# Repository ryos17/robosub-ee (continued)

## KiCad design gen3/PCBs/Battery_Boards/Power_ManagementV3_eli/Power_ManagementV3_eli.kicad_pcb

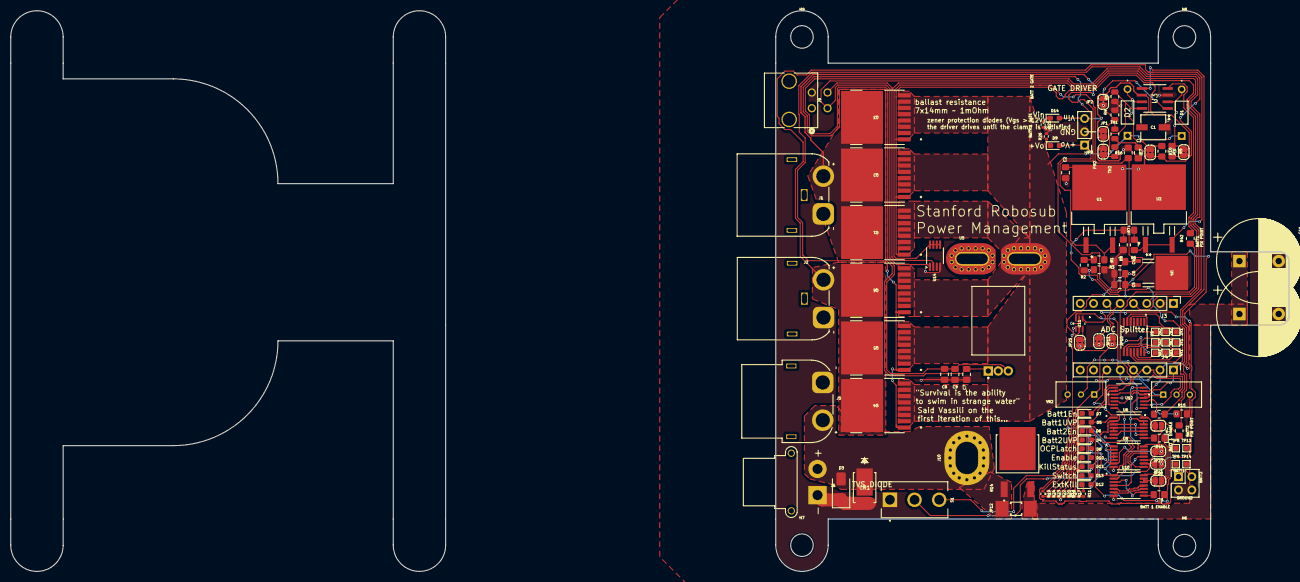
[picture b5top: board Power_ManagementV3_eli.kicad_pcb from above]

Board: 2 copper layers, 98.0 x 107.0 mm, 118 parts (0 on the bottom side), 73 nets.

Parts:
2A2, 2B2, 2Y1, 3A2, 3B2, 3Y1, 4A1, 4B1, 4Y1: TestPoint; TestPoint_Pad_1.0x1.0mm
C1: 10uF; CAP_EEE-1CA100SR_PAN
C2, C3, C4, C5: 10uF; C_0805_2012Metric_Pad1.18x1.45mm_HandSolder
C6: 1uF; C_0805_2012Metric_Pad1.18x1.45mm_HandSolder
C7: 0.1u; C_0805_2012Metric_Pad1.18x1.45mm_HandSolder
C8: 100nF; C_0805_2012Metric_Pad1.18x1.45mm_HandSolder
C9: 1µF; C_0805_2012Metric_Pad1.18x1.45mm_HandSolder
C10, C11: 10,000uF; CP_Radial_D16.0mm_P7.50mm
CR1: SBRT15U50SP5-13; POWERDI5_DIO
D1, D2: D_Zener; 1N5242B
D3: TVS; D_SMA
D4, D5, D6, D7, D8, D9, D10, D11, D12, D13, D14: GreenLED; LED_0603_1608Metric_Pad1.05x0.95mm_HandSolder
H6, H7, H8, H9: MountingHole; MountingHole_4.3mm_M4
J1, J2: Conn_01x02_Pin; AMASS_XT60IPW-M_1x03_P7.20mm_Horizontal
J3, J4: Conn_01x08; PinHeader_1x08_P2.54mm_Vertical
J5: Conn_01x02_Pin; AMASS_XT60PW-F_1x02_P7.20mm_Horizontal
J6: Conn_01x02_Pin; AMASS_XT30PW-F_1x02_P2.50mm_Horizontal
J9: Conn_01x04_Pin; CONN_SD-43045-008_04_MOL
J10: via; MountingHole_4.3x6.2mm_M4_Pad_Via
J17: FPGA MOUNT; PinHeader_2x02_P2.54mm_Vertical
JP1, JP3: SolderJumper_2_Bridged; SolderJumper-2_P1.3mm_Bridged2Bar_RoundedPad1.0x1.5mm
JP2: SolderJumper_2_Open; SolderJumper-2_P1.3mm_Open_RoundedPad1.0x1.5mm
JP6, JP7: SolderJumper-2_P1.3mm_Bridged2Bar_RoundedPad1.0x1.5mm
JP10, JP11, JP25, JP27: Jumper_2_Bridged; SolderJumper-2_P1.3mm_Bridged2Bar_RoundedPad1.0x1.5mm
JP12: Jumper_2_Open; KEYSTONE_5102
JP21, JP23, JP26: Jumper_2_Open; SolderJumper-2_P1.3mm_Open_RoundedPad1.0x1.5mm
PM2: LMS78
Q1, Q2, Q3, Q4, Q5, Q6: MCTL160N15Y-TP; TOLL-8L_MCC
R1, R6: 50k; R_0805_2012Metric_Pad1.20x1.40mm_HandSolder
R2, R3, R7, R8, R16: 10k; R_0805_2012Metric_Pad1.20x1.40mm_HandSolder
R4, R5: 100k; R_0805_2012Metric
R9, R10, R42, R43, R44, R45: 0R; R_0805_2012Metric_Pad1.20x1.40mm_HandSolder
R11, R12, R17, R18, R19, R20, R22, R23, R24: 100; R_0402_1005Metric
R13: 2.2k; R_0805_2012Metric_Pad1.20x1.40mm_HandSolder
R14: 0.5 Ohm 25W; TO508P1229X317-3N
R15: 3.9k; R_0805_2012Metric_Pad1.20x1.40mm_HandSolder
R25: 15k; R_0402_1005Metric
R26: 1.5k; R_0402_1005Metric
S1: 100SP1T1B4M2QE; SW_100SP1T1B4M2QE
TH1, TH2: Thermistor_US; R_0805_2012Metric
TP8, TP9, TP13, TP14: TestPoint; TestPoint_Pad_1.0x1.0mm
U1, U2: STPS5045SG-TR; D2PAK_STM
U3: LTC1255CS8-PBF; LTC1255
U4: BA033CC0FP-E2; TO252-3_ROM
U5: ACS758LCB-100U-PFF-T; Allegro_MicroSystems,_LLC-CB-5-PFF-0-0-MFG
U6, U8, U9, U10: SN74HC132PWR; SOP65P640X120-14N
U11: SN74LVC1G373DCKR; SN74LVC
U12: MCP6564-E/ST; TSSOP14_MC_MCH
U14: MCP9808_MSOP; MSOP-8_3x3mm_P0.65mm
VR1, VR2: 3296W-1-103RLF; TRIM_3296W-1-103RLF

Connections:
+3.3V: C5.1, C6.1, JP10.2 (B), JP21.2 (B), JP23.2 (B), R16.1, S1.3, U4.3 (OUT), U6.14 (VCC), U8.14 (VCC), U9.14 (VCC), U10.14 (VCC), U11.5 (VCC), U12.4 (VDD), U14.5 (A2), U14.6 (A1), U14.7 (A0), U14.8 (V_{DD}), VR1.1, VR2.1
+5V: C4.1, C7.2, D9.2 (A), PM2.3, U4.1 (Vcc), U5.1 (VCC)
+BATT: CR1.3, D3.2 (A), J5.2, J6.2, J10.1, JP12.2 (B), R14.1, U5.5 (IP-)
+BATT1: J1.2, Q1.9 (D), Q2.9 (D), Q3.9 (D), R1.2, U1.1 (Input), U1.3 (Input)
+BATT2: J2.2, Q4.9 (D), Q5.9 (D), Q6.9 (D), R6.1, U2.1 (Input), U2.3 (Input)
+BATTHall: D1.2 (A), D2.2 (A), Q1.2 (S), Q1.3 (S), Q1.4 (S), Q1.5 (S), Q1.6 (S), Q1.7 (S), Q1.8 (S), Q2.2 (S), Q2.3 (S), Q2.4 (S), Q2.5 (S), Q2.6 (S), Q2.7 (S), Q2.8 (S), Q3.2 (S), Q3.3 (S), Q3.4 (S), Q3.5 (S), Q3.6 (S), Q3.7 (S), Q3.8 (S), Q4.2 (S), Q4.3 (S), Q4.4 (S), Q4.5 (S), Q4.6 (S), Q4.7 (S), Q4.8 (S), Q5.2 (S), Q5.3 (S), Q5.4 (S), Q5.5 (S), Q5.6 (S), Q5.7 (S), Q5.8 (S), Q6.2 (S), Q6.3 (S), Q6.4 (S), Q6.5 (S), Q6.6 (S), Q6.7 (S), Q6.8 (S), U5.4 (IP+)
+VregDiode: C1.1, C2.1, C3.1, D14.2 (A), JP1.2 (B), JP3.2 (B), PM2.1, TH1.1, TH2.1, U1.2 (Output), U2.2 (Output), U3.6 (VS)
-BATT1: C1.2, C2.2, C3.2, C4.2, C5.2, C6.2, C7.1, C8.2, C9.2, C10.2, C11.2, CR1.1, CR1.2, D3.1 (K), J1.1, J2.1, J3.2, J5.1, J6.1, J9.2, J17.3, J17.4, JP11.2 (B), JP25.1 (A), PM2.2, R3.1, R4.1, R5.1, R8.1, R11.2, R12.1, R15.2, R16.2, R17.2, R18.2, R19.2, R20.2, R22.2, R23.2, R24.2, R25.2, R26.2, S1.1, U3.3 (GND), U4.2 (GND), U5.2 (GND), U6.7 (GND), U8.7 (GND), U9.7 (GND), U10.7 (GND), U11.2 (GND), U12.11 (VSS), U14.4 (GND), VR1.3, VR2.3
/Battery Control Logic/Batt1>UVP: D5.2 (A), U6.1 (1A), U12.8 (OUTC)
/Battery Control Logic/Batt1Disable: U10.5 (2B), U10.11 (4Y)
/Battery Control Logic/Batt2>UVP: D4.2 (A), U10.1 (1A), U12.14 (OUTD)
/Battery Control Logic/OCPReference: J4.4, U12.2 (-INA), VR2.2
/Battery Control Logic/OnboardKillSwitch: D13.2 (A), S1.2, U8.1 (1A)
/Battery Control Logic/UVPReference: J4.3, U12.9 (-INC), U12.13 (-IND), VR1.2
/Battery Control Logic/VBatt1 > VBatt2: U6.4 (2A), U6.5 (2B), U6.11 (4Y)
/Battery Control Logic/VBatt1<VBatt2: U6.12 (4A), U6.13 (4B), U10.4 (2A), U12.7 (OUTB)
/Battery Control Logic/pre_enable1: R44.2, U6.8 (3Y)
/Battery Control Logic/pre_enable2: R45.2, U10.8 (3Y)
/Battery Control Logic/~GateDisable: D10.2 (A), J4.6, U6.2 (1B), U8.11 (4Y), U10.2 (1B)
/Battery Control Logic/~OCP: J4.5, U11.3 (D), U12.1 (OUTA)
/Battery Control Logic/~SystemKill post: JP27.2 (B), U8.10 (3B)
/ENABLE_BATT1: R42.2, U3.4 (IN1)
/ENABLE_BATT2: R43.2, U3.5 (IN2)
Batt1Enable: D7.2 (A), J17.1, JP21.1 (A), R42.1, R44.1, U10.12 (4A), U10.13 (4B)
Batt1Gate: JP6.1 (A), Q1.1 (G), Q2.1 (G), Q3.1 (G), R9.2
Batt1GatePreDiv: D1.1 (K), JP6.2 (B), R9.1, U3.2 (GATE1)
Batt2Enable: D6.2 (A), J17.2, JP23.1 (A), R43.1, R45.1
Batt2Gate: JP7.1 (A), Q4.1 (G), Q5.1 (G), Q6.1 (G), R10.2
Batt2GatePreDiv: D2.1 (K), JP7.2 (B), R10.1, U3.7 (GATE2)
COM: J3.6, JP11.1 (A)
Capacitors: C10.1, C11.1, JP12.1 (A), R14.2
I2C1_SCL: J3.3, J9.4, U14.2 (SCL)
I2C1_SDA: J3.4, J9.3, U14.1 (SDA)
ISample3.3V: R13.2, R15.1, U12.3 (+INA)
ISample5V: C8.1, C9.1, R13.1, U5.3 (VIOUT)
KillSwitch: D12.2 (A), U8.2 (1B)
LETeensy: JP26.1 (A), U11.1 (LE)
unnamed: D7.1 (K), R19.1
unnamed: D9.1 (K), R26.1
unnamed: D14.1 (K), R25.1
unnamed: JP1.1 (A), JP2.1 (A), R4.2, TH1.2, U3.1 (DS1)
unnamed: JP2.2 (B), JP3.1 (A), R5.2, TH2.2, U3.8 (DS2)
unnamed: JP25.2 (B), U11.6 (*OE)
unnamed: R1.1, R2.1
unnamed: R6.2, R7.2
unnamed: U6.3 (1Y), U6.9 (3A)
unnamed: U6.6 (2Y), U6.10 (3B)
unnamed: U8.3 (1Y), U8.4 (2A), U8.5 (2B)
unnamed: U8.8 (3Y), U8.12 (4A), U8.13 (4B)
unnamed: 2A2.1, U9.4 (2A)
unnamed: 2B2.1, U9.5 (2B)
unnamed: 2Y1.1, U9.6 (2Y)
unnamed: 3A2.1, U9.9 (3A)
unnamed: 3B2.1, U9.10 (3B)
unnamed: 3Y1.1, U9.8 (3Y)
unnamed: 4A1.1, U9.12 (4A)
unnamed: 4B1.1, U9.13 (4B)
unnamed: 4Y1.1, U9.11 (4Y)
unnamed: U10.3 (1Y), U10.9 (3A)
unnamed: U10.6 (2Y), U10.10 (3B)
RArray1: D12.1 (K), R11.1
RArray2: D13.1 (K), R12.2
RArray3: D11.1 (K), R17.1
RArray4: D10.1 (K), R18.1
RArray5: D8.1 (K), R20.1
RArray6: D4.1 (K), R22.1
RArray7: D6.1 (K), R23.1
RArray8: D5.1 (K), R24.1
REF: J3.5, JP10.1 (A)
VSampleBatt1: J4.2, R2.2, R3.2, U12.6 (-INB), U12.10 (+INC)
VSampleBatt2: J4.1, R7.1, R8.2, U12.5 (+INB), U12.12 (+IND)
~OCPLatch: D8.2 (A), JP26.2 (B), U8.9 (3A), U11.4 (Q)
~SystemKill: D11.2 (A), JP27.1 (A), U8.6 (2Y)

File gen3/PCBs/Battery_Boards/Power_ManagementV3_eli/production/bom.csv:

Designator,Footprint,Quantity,Value,LCSC Part #
"2A2, 2B2, 2Y1, 3A2, 3B2, 3Y1, 4A1, 4B1, 4Y1, TP13, TP14, TP8, TP9",TestPoint_Pad_1.0x1.0mm,13,TestPoint,
C1,CAP_EEE-1CA100SR_PAN,1,10uF,
"C10, C11",CP_Radial_D16.0mm_P7.50mm,2,"10,000uF",
"C2, C3, C4, C5",0805,4,10uF,
C6,0805,1,1uF,
C7,0805,1,0.1u,
C8,0805,1,100nF,
C9,0805,1,1µF,
CR1,POWERDI5_DIO,1,SBRT15U50SP5-13,
"D1, D2",1N5242B,2,D_Zener,
"D10, D11, D12, D13, D14, D4, D5, D6, D7, D8, D9",0603,11,GreenLED,
D3,D_SMA,1,TVS,
"H6, H7, H8, H9",MountingHole_4.3mm_M4,4,MountingHole,
"J1, J2",AMASS_XT60IPW-M_1x03_P7.20mm_Horizontal,2,Conn_01x02_Pin,
J10,MountingHole_4.3x6.2mm_M4_Pad_Via,1,via,
J17,PinHeader_2x02_P2.54mm_Vertical,1,FPGA MOUNT,
"J3, J4",PinHeader_1x08_P2.54mm_Vertical,2,Conn_01x08,
J5,AMASS_XT60PW-F_1x02_P7.20mm_Horizontal,1,Conn_01x02_Pin,
J6,AMASS_XT30PW-F_1x02_P2.50mm_Horizontal,1,Conn_01x02_Pin,
J9,CONN_SD-43045-008_04_MOL,1,Conn_01x04_Pin,
"JP10, JP11, JP25, JP27",SolderJumper-2_P1.3mm_Bridged2Bar_RoundedPad1.0x1.5mm,4,Jumper_2_Bridged,
JP12,KEYSTONE_5102,1,Jumper_2_Open,
"JP21, JP23, JP26",SolderJumper-2_P1.3mm_Open_RoundedPad1.0x1.5mm,3,Jumper_2_Open,
"JP6, JP7",SolderJumper-2_P1.3mm_Bridged2Bar_RoundedPad1.0x1.5mm,2,~,
PM2,LMS78,1,LMS78,
"Q1, Q2, Q3, Q4, Q5, Q6",TOLL-8L_MCC,6,MCTL160N15Y-TP,
"R1, R6",0805,2,50k,
"R10, R42, R43, R44, R45, R9",0805,6,0R,
"R11, R12, R17, R18, R19, R20, R22, R23, R24",0402,9,100,
R13,0805,1,2.2k,
R14,TO508P1229X317-3N,1,0.5 Ohm 25W,
R15,0805,1,3.9k,
"R16, R2, R3, R7, R8",0805,5,10k,
R25,0402,1,15k,
R26,0402,1,1.5k,
"R4, R5",0805,2,100k,
S1,SW_100SP1T1B4M2QE,1,100SP1T1B4M2QE,
"TH1, TH2",0805,2,Thermistor_US,
"U1, U2",D2PAK_STM,2,STPS5045SG-TR,
"U10, U6, U8, U9",SOP65P640X120-14N,4,SN74HC132PWR,
U11,SN74LVC,1,SN74LVC1G373DCKR,
U12,TSSOP14_MC_MCH,1,MCP6564-E/ST,
U14,MSOP-8_3x3mm_P0.65mm,1,MCP9808_MSOP,
U3,LTC1255,1,LTC1255CS8-PBF,
U4,TO252-3_ROM,1,BA033CC0FP-E2,
U5,"Allegro_MicroSystems,_LLC-CB-5-PFF-0-0-MFG",1,ACS758LCB-100U-PFF-T,
"VR1, VR2",TRIM_3296W-1-103RLF,2,3296W-1-103RLF,

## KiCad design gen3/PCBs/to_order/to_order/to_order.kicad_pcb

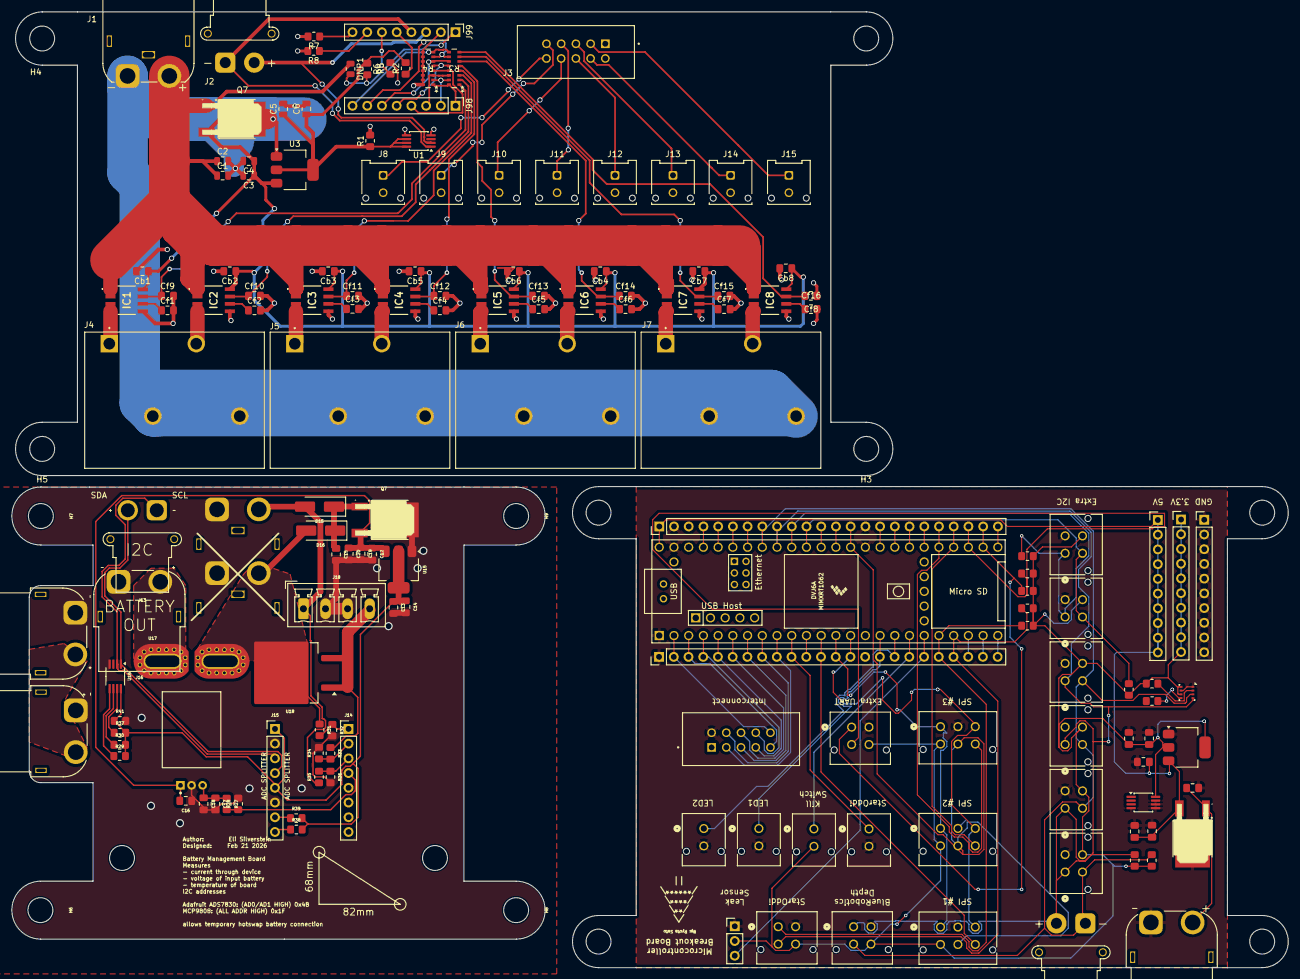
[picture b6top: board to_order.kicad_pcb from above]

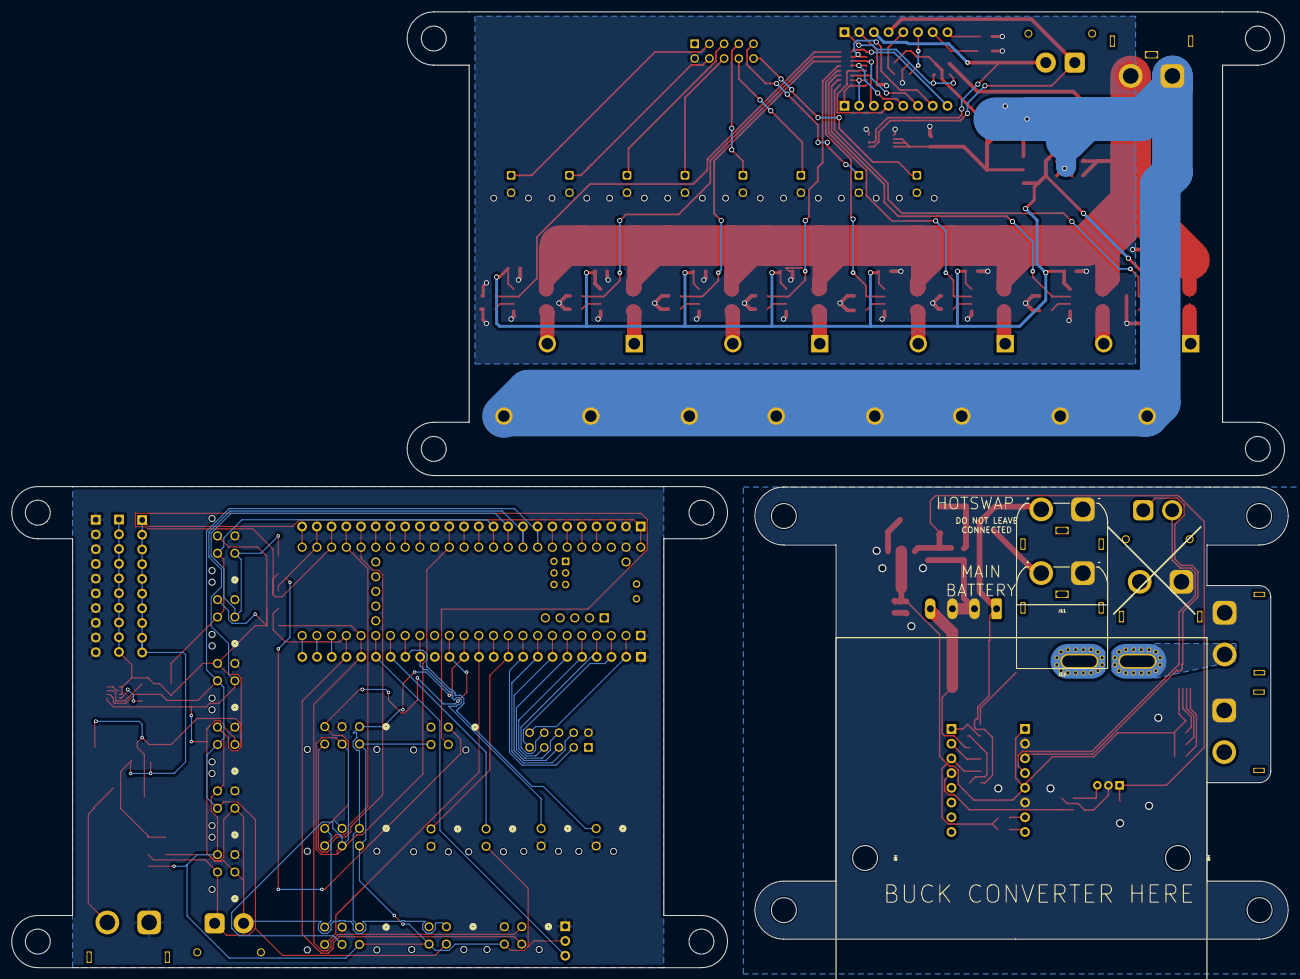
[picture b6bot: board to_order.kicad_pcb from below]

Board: 2 copper layers, 220.2 x 164.9 mm, 166 parts (4 on the bottom side), 109 nets.

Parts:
C1, C12, C12#2, C13, C13#2, C15, C15#2, C19: 10uF; C_0805_2012Metric_Pad1.18x1.45mm_HandSolder
C1#2, C3, C5: 1 µF; C_0805_2012Metric
C2, C14, C14#2, C20: 1uF; C_0805_2012Metric_Pad1.18x1.45mm_HandSolder
C2#2, C4, C6: 10 µF; C_0805_2012Metric
C16: 0.1uF; C_0805_2012Metric_Pad1.18x1.45mm_HandSolder
C17: 100nF; C_0805_2012Metric_Pad1.18x1.45mm_HandSolder
C18: 1µF; C_0805_2012Metric_Pad1.18x1.45mm_HandSolder
Cb1, Cb2, Cb3, Cb4, Cb5, Cb6, Cb7, Cb8: 0.1 µF; C_0805_2012Metric_Pad1.18x1.45mm_HandSolder
Cf1, Cf2, Cf3, Cf4, Cf5, Cf6, Cf7, Cf8: 100 nF; C_0805_2012Metric_Pad1.18x1.45mm_HandSolder
Cf9, Cf10, Cf11, Cf12, Cf13, Cf14, Cf15, Cf16: 1 µF; C_0805_2012Metric_Pad1.18x1.45mm_HandSolder
D15, D16: SS54; D_SMA_Handsoldering
DNP1: 0; R_0805_2012Metric
H2, H3, H4, H5, H6, H6#2, H7, H7#2, H8, H8#2, H8#3, H8#4, H9, H9#2: MountingHole; MountingHole_4.3mm_M4
IC1, IC2, IC3, IC4, IC5, IC6, IC7, IC8: ACS713ELCTR-30A-T; ACS711ELCTR25ABT
J1, J11#3, J12#3: Conn_01x02_Pin; AMASS_XT60IPW-M_1x03_P7.20mm_Horizontal
J1#2: BlueRobotics Depth Sensor; CONN_SD-43045-005_04_MOL
J2, J13#2: Conn_01x02_Pin; AMASS_XT30PW-F_1x02_P2.50mm_Horizontal
J2#2: Interconnect; SULLINS_SBH11-PBPC-D05-ST-BK
J3: External Battery; AMASS_XT60PW-F_1x02_P7.20mm_Horizontal
J3#2: SBH11-PBPC-D05-ST-BK; SULLINS_SBH11-PBPC-D05-ST-BK
J4, J5#2, J6, J7#2: 1098169; PHOENIX_1098169
J4#2, J6#2: Conn_01x24; PinHeader_1x24_P2.54mm_Vertical
J5: External I2C; AMASS_XT30PW-F_1x02_P2.50mm_Horizontal
J7: Extra I2C #1; CONN_SD-43045-005_04_MOL
J8: 0430450212; Molex_Micro-Fit_3.0_43045-0212_2x01_P3.00mm_Vertical
J8#2: Extra I2C #2; CONN_SD-43045-005_04_MOL
J9: Lumen PWM; CONN_SD-43045-005_02_MOL
J9#2, J10, J11#2, J12#2, J13#3, J14#2, J15: 430450228; Molex_Micro-Fit_3.0_43045-0212_2x01_P3.00mm_Vertical
J10#2: Kill Switch; CONN_SD-43045-005_02_MOL
J11: StarOddi CTD Comms; CONN_SD-43045-005_04_MOL
J12: LED1; CONN_SD-43045-005_02_MOL
J13: LED2; CONN_SD-43045-005_02_MOL
J14: Leak Sensor; PinHeader_1x03_P2.54mm_Vertical
J14#3, J15#2, J98, J99: Conn_01x08; PinHeader_1x08_P2.54mm_Vertical
J15#3: Extra I2C #3; CONN_SD-43045-005_04_MOL
J16: Extra I2C #6; CONN_SD-43045-005_04_MOL
J16#2, J21#2, J22: Conn_01x02_Pin; AMASS_XT60PW-F_1x02_P7.20mm_Horizontal
J17: Extra I2C #5; CONN_SD-43045-005_04_MOL
J18: Extra I2C #4; CONN_SD-43045-005_04_MOL
J18#2: Conn_01x04_Socket; PhoenixContact_MCV_1,5_4-G-3.81_1x04_P3.81mm_Vertical
J19: GND Line; PinHeader_1x10_P2.54mm_Vertical
J20: 3.3V Line; PinHeader_1x10_P2.54mm_Vertical
J21: 5V Line; PinHeader_1x10_P2.54mm_Vertical
J22#2: Extra SPI #1; CONN_SD-43045-005_06_MOL
J23: Extra SPI #2; CONN_SD-43045-005_06_MOL
J24: Extra SPI #3; CONN_SD-43045-005_06_MOL
J25: Secondary UART; CONN_SD-43045-005_04_MOL
Q7, Q7#2, Q7#3: L78M05ABDT-TR; TO-252-2_L6.5-W6.1-P4.58-LS10.0-TL
R1, R2, R3#2, R4#2, R5#2, R6#2, R7, R8, R10, R11, R27, R32, R34, R36, R41: 10k; R_0805_2012Metric_Pad1.20x1.40mm_HandSolder
R1#2, R2#2, R5, R6, R7#2, R8#2, R29, R30, R37, R38, R39: 0R; R_0805_2012Metric_Pad1.20x1.40mm_HandSolder
R3: 2.2k Array; 2506_8x_Resistor_Array
R4: 3.3k Array; 2506_8x_Resistor_Array
R28: 20k; R_0805_2012Metric_Pad1.20x1.40mm_HandSolder
R31, R33, R35: 47k; R_0805_2012Metric_Pad1.20x1.40mm_HandSolder
U1, U2, U16: MCP9808_MSOP; MSOP-8_3x3mm_P0.65mm
U3, U15, U15#2: AMS1117-3.3; SOT-223-3_TabPin2
U4: BME280; Bosch_LGA-8_2.5x2.5mm_P0.65mm_ClockwisePinNumbering
U6: Teensy4.1; Teensy41
U17: ACS758LCB-100U-PFF-T; Allegro_MicroSystems,_LLC-CB-5-PFF-0-0-MFG
U18: SRT60L100DC-R; TO-263-2

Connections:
+3.3V: C5.1, C6.1, C13#2.1, C14#2.1, J1#2.4, J7.4, J8#2.4, J10#2.2, J11.4, J14.2, J15#3.4, J16.4, J17.4, J18.4, J20.1, J20.2, J20.3, J20.4, J20.5, J20.6, J20.7, J20.8, J20.9, J20.10, J22#2.4, J23.4, J24.4, J25.4, R1.1, R2.1, R2#2.2, R3#2.1, R4#2.1, R5#2.1, R6.1, R6#2.1, R7.2, R8.2, R10.2, R11.2, U1.6 (A1), U1.7 (A0), U1.8 (V_{DD}), U2.8 (V_{DD}), U3.2 (VO), U4.6 (VDDIO), U4.8 (VDD), U15.2 (VO)
+3.3V_: C13.1, C14.1, J15#2.1, J15#2.5, R29.2, R30.2, R37.2, R38.2, R39.2, R41.1, U15#2.2 (VO), U16.8 (V_{DD})
+5V: C1.1, C2.1, C3.1, C4.1, C12.1, Cb1.1, Cb2.1, Cb3.1, Cb4.1, Cb5.1, Cb6.1, Cb7.1, Cb8.1, DNP1.1, IC1.8 (VCC), IC2.8 (VCC), IC3.8 (VCC), IC4.8 (VCC), IC5.8 (VCC), IC6.8 (VCC), IC7.8 (VCC), IC8.8 (VCC), J6#2.1, J21.1, J21.2, J21.3, J21.4, J21.5, J21.6, J21.7, J21.8, J21.9, J21.10, Q7#2.3 (OUT), Q7#3.3 (OUT), U3.3 (VI), U6.48 (VIN), U15.3 (VI)
+5V_: C12#2.1, C16.2, C19.1, C20.1, Q7.3 (OUT), U15#2.3 (VI), U17.1 (VCC)
+BATT: C1#2.1, C2#2.1, D16.2 (A), IC1.1 (IP+_1), IC1.2 (IP+_2), IC2.1 (IP+_1), IC2.2 (IP+_2), IC3.1 (IP+_1), IC3.2 (IP+_2), IC4.1 (IP+_1), IC4.2 (IP+_2), IC5.1 (IP+_1), IC5.2 (IP+_2), IC6.1 (IP+_1), IC6.2 (IP+_2), IC7.1 (IP+_1), IC7.2 (IP+_2), IC8.1 (IP+_1), IC8.2 (IP+_2), J1.2, J12#3.2, Q7#3.1 (IN), R31.1, U17.4 (IP+), U18.2 (Output)
+BATT_out: J16#2.2, J21#2.2, J22.2, U17.5 (IP-)
+EXT_LV_SUPPLY: J18#2.4, R33.1, U18.1 (Input), U18.3 (Input)
+TEMP_BATT: D15.2 (A), J11#3.2, J18#2.1, R35.1
-BATT: C1#2.2, C2#2.2, C3.2, C4.2, C5.2, C6.2, J1.1, J4.2, J4.4, J5#2.2, J5#2.4, J6.2, J6.4, J7#2.2, J7#2.4, Q7#3.4 (GND), U3.1 (GND)
/SCL: J13#2.1, J15#2.3, U16.2 (SCL)
/SDA: J13#2.2, J15#2.4, U16.1 (SDA)
AD0: J99.7, R8#2.1
AD1: J99.8, R7#2.1
COM: J99.6, R5.1
Dled1: J4#2.16, J12.1, U6.16 (24_A10_TX6_SCL2)
Dled2: J4#2.17, J13.1, U6.17 (25_A11_RX6_SDA2)
Dswitch1: J4#2.18, J10#2.1, U6.18 (26_A12_MOSI1)
GND: C1.2, C2.2, C12.2, C13#2.2, C14#2.2, C15#2.2, Cb1.2, Cb2.2, Cb3.2, Cb4.2, Cb5.2, Cb6.2, Cb7.2, Cb8.2, Cf1.2, Cf2.2, Cf3.2, Cf4.2, Cf5.2, Cf6.2, Cf7.2, Cf8.2, Cf9.2, Cf10.2, Cf11.2, Cf12.2, Cf13.2, Cf14.2, Cf15.2, Cf16.2, IC1.5 (GND), IC2.5 (GND), IC3.5 (GND), IC4.5 (GND), IC5.5 (GND), IC6.5 (GND), IC7.5 (GND), IC8.5 (GND), J1#2.2, J2#2.2, J3.1, J3#2.2, J4#2.1, J6#2.2, J6#2.15, J7.2, J8.2, J8#2.2, J9.2, J9#2.2, J10.2, J11.2, J11#2.2, J12.2, J12#2.2, J13.2, J13#3.2, J14.1, J14#2.2, J15.2, J15#3.2, J16.2, J17.2, J18.2, J19.1, J19.2, J19.3, J19.4, J19.5, J19.6, J19.7, J19.8, J19.9, J19.10, J22#2.2, J23.2, J24.2, J25.2, J99.2, Q7#2.4 (GND), R1.2, R4.9, R4.10, R4.11, R4.12, R4.13, R4.14, R4.15, R4.16, R5.2, R7#2.2, R8#2.2, U1.4 (GND), U1.5 (A2), U2.4 (GND), U2.5 (A2), U2.6 (A1), U2.7 (A0), U4.1 (GND), U4.7 (GND), U6.1 (GND), U6.34 (GND), U6.47 (GND), U15.1 (GND)
GND_bak: C12#2.2, C13.2, C14.2, C15.2, C16.1, C17.2, C18.2, C19.2, C20.2, J11#3.1, J12#3.1, J15#2.2, J15#2.6, J16#2.1, J18#2.2, J18#2.3, J21#2.1, J22.1, Q7.4 (GND), R28.2, R32.2, R34.2, R36.2, R41.2, U15#2.1 (GND), U16.4 (GND), U17.2 (GND)
I2C1_SCL: J1#2.3, J5.1, J6#2.8, J7.3, J8#2.3, J15#3.3, J18.3, R5#2.2, U4.3 (SDI), U6.41 (19_A5_SCL)
I2C1_SDA: J1#2.1, J5.2, J6#2.9, J7.1, J8#2.1, J15#3.1, J18.1, R4#2.2, U4.4 (SCK), U6.40 (18_A4_SDA)
I2C2_SCL: J6#2.11, J16.3, J17.3, R3#2.2, U6.38 (16_A2_RX4_SCL1)
I2C2_SDA: J6#2.10, J16.1, J17.1, R6#2.2, U6.39 (17_A3_TX4_SDA1)
Lumen_PWM: J4#2.10, J9.1, U6.10 (8_TX2_IN1)
unnamed: C15.1, D15.1 (K), D16.1 (K), Q7.1 (IN)
unnamed: Cf1.1, IC1.6 (FILTER)
unnamed: Cf2.1, IC2.6 (FILTER)
unnamed: Cf3.1, IC3.6 (FILTER)
unnamed: Cf4.1, IC4.6 (FILTER)
unnamed: Cf5.1, IC5.6 (FILTER)
unnamed: Cf6.1, IC6.6 (FILTER)
unnamed: Cf7.1, IC7.6 (FILTER)
unnamed: Cf8.1, IC8.6 (FILTER)
unnamed: J14#3.1, R31.2, R32.1
unnamed: J14#3.2, R33.2, R34.1
unnamed: J14#3.3, R35.2, R36.1
unnamed: J15#2.7, R39.1
unnamed: J15#2.8, R38.1
unnamed: DNP1.2, J99.1, R6.2
unnamed: R2.2, U4.2 (CSB)
unnamed: R1#2.2, U4.5 (SDO)
unnamed: R37.1, U16.7 (A0)
unnamed: R30.1, U16.6 (A1)
unnamed: R29.1, U16.5 (A2)
PIN9: J4#2.11, U6.11 (9_OUT1C)
PIN14: J6#2.13, U6.36 (14_A0_TX3_SPDIF_OUT)
PIN15: J6#2.12, U6.37 (15_A1_RX3_SPDIF_IN)
PIN20: J6#2.7, U6.42 (20_A6_TX5_LRCLK1)
PIN21: J6#2.6, U6.43 (21_A7_RX5_BCLK1)
PIN22: J6#2.5, U6.44 (22_A8_CTX1)
PIN23: J6#2.4, U6.45 (23_A9_CRX1_MCLK1)
PIN30: J4#2.22, U6.22 (30_CRX3)
PIN31: J4#2.23, U6.23 (31_CTX3)
PIN32: J4#2.24, U6.24 (32_OUT1B)
PIN33: J6#2.24, U6.25 (33_MCLK2)
PIN38: J6#2.19, U6.30 (38_CS1_IN1)
PIN39: J6#2.18, U6.31 (39_MISO1_OUT1A)
PIN40: J6#2.17, U6.32 (40_A16)
PIN41: J6#2.16, U6.33 (41_A17)
PWM0: J2#2.10, J4#2.2, U6.2 (0_RX1_CRX2_CS1)
PWM1: J2#2.9, J3#2.10, J4#2.3, J8.1, U6.3 (1_TX1_CTX2_MISO1)
PWM2: J2#2.8, J3#2.9, J4#2.4, J9#2.1, U6.4 (2_OUT2)
PWM3: J2#2.7, J3#2.8, J4#2.5, J10.1, U6.5 (3_LRCLK2)
PWM4: J2#2.6, J3#2.7, J4#2.6, J11#2.1, U6.6 (4_BCLK2)
PWM5: J2#2.5, J3#2.6, J4#2.7, J12#2.1, U6.7 (5_IN2)
PWM6: J2#2.4, J3#2.5, J4#2.8, J13#3.1, U6.8 (6_OUT1D)
PWM7: J2#2.3, J3#2.4, J4#2.9, J14#2.1, U6.9 (7_RX2_OUT1A)
PWM8: J3#2.3, J15.1
PWR1: IC1.3 (IP-_1), IC1.4 (IP-_2), J4.1
PWR2: IC2.3 (IP-_1), IC2.4 (IP-_2), J4.3
PWR3: IC3.3 (IP-_1), IC3.4 (IP-_2), J5#2.1
PWR4: IC4.3 (IP-_1), IC4.4 (IP-_2), J5#2.3
PWR5: IC5.3 (IP-_1), IC5.4 (IP-_2), J6.1
PWR6: IC6.3 (IP-_1), IC6.4 (IP-_2), J6.3
PWR7: IC7.3 (IP-_1), IC7.4 (IP-_2), J7#2.1
PWR8: IC8.3 (IP-_1), IC8.4 (IP-_2), J7#2.3
REF: J99.5, R2#2.1
SCL: J2.2, J99.3, U1.2 (SCL)
SDA: J2.1, J99.4, U1.1 (SDA)
SPI_CS1: J4#2.12, J22#2.6, U6.12 (10_CS_MQSR)
SPI_CS2: J6#2.21, J23.6, U6.28 (36_CS)
SPI_CS3: J6#2.20, J24.6, U6.29 (37_CS)
SPI_MISO: J4#2.14, J22#2.3, J23.3, J24.3, U6.14 (12_MISO_MQSL)
SPI_MOSI: J4#2.13, J22#2.1, J23.1, J24.1, U6.13 (11_MOSI_CTX1)
SPI_SCK: J6#2.14, J22#2.5, J23.5, J24.5, U6.35 (13_SCK_LED)
UART_RX1: J4#2.20, J11.1, R11.1, U6.20 (28_RX7)
UART_RX2: J6#2.23, J25.1, R8.1, U6.26 (34_RX8)
UART_TX1: J4#2.21, J11.3, R10.1, U6.21 (29_TX7)
UART_TX2: J6#2.22, J25.3, R7.1, U6.27 (35_TX8)
VIout1: Cf9.1, IC1.7 (VIOUT), R3.1
VIout1Div: J98.1, R3.16, R4.1
VIout2: Cf10.1, IC2.7 (VIOUT), R3.2
VIout2Div: J98.2, R3.15, R4.2
VIout3: Cf11.1, IC3.7 (VIOUT), R3.3
VIout3Div: J98.3, R3.14, R4.3
VIout4: Cf12.1, IC4.7 (VIOUT), R3.4
VIout4Div: J98.4, R3.13, R4.4
VIout5: Cf13.1, IC5.7 (VIOUT), R3.5
VIout5Div: J98.5, R3.12, R4.5
VIout6: Cf14.1, IC6.7 (VIOUT), R3.6
VIout6Div: J98.6, R3.11, R4.6
VIout7: Cf15.1, IC7.7 (VIOUT), R3.7
VIout7Div: J98.7, R3.10, R4.7
VIout8: Cf16.1, IC8.7 (VIOUT), R3.8
VIout8Div: J98.8, R3.9, R4.8
V_BATT: C15#2.1, J3.2, Q7#2.1 (IN)
current_sensor_3v3: J14#3.4, R27.2, R28.1
current_sensor_5v: C17.1, C18.1, R27.1, U17.3 (VIOUT)
xDleak: J4#2.19, J14.3, U6.19 (27_A13_SCK1)

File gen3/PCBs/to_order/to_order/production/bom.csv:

Designator,Footprint,Quantity,Value,LCSC Part #
"C1_2, C12_2, C12, C13_2, C13, C15_2, C15, C19",0805,8,10uF,
"C1, C3, C5, CF10, CF11, CF12, CF13, CF14, CF15, CF16, CF9",0805,11,1 µF,
"C14_2, C14, C2_2, C20",0805,4,1uF,
C16,0805,1,0.1uF,
C17,0805,1,100nF,
C18,0805,1,1µF,
"C2, C4, C6",0805,3,10 µF,
"CB1, CB2, CB3, CB4, CB5, CB6, CB7, CB8",0805,8,0.1 µF,
"CF1, CF2, CF3, CF4, CF5, CF6, CF7, CF8",0805,8,100 nF,
"D15, D16",D_SMA_Handsoldering,2,SS54,
DNP1,0805,1,0,
"H2, H3, H4, H5, H6_2, H6, H7_2, H7, H8_4, H8_3, H8_2, H8, H9_2, H9",MountingHole_4.3mm_M4,14,MountingHole,
"IC1, IC2, IC3, IC4, IC5, IC6, IC7, IC8",ACS711ELCTR25ABT,8,ACS713ELCTR-30A-T,
"J1_2, J11, J12",AMASS_XT60IPW-M_1x03_P7.20mm_Horizontal,3,Conn_01x02_Pin,
J1,CONN_SD-43045-005_04_MOL,1,BlueRobotics Depth Sensor,
"J10_2, J11_2, J12_2, J13, J14_2, J15_3, J9",Molex_Micro-Fit_3.0_43045-0212_2x01_P3.00mm_Vertical,7,430450228,
J10,CONN_SD-43045-005_02_MOL,1,Kill Switch,
J11_3,CONN_SD-43045-005_04_MOL,1,StarOddi CTD Comms,
J12_3,CONN_SD-43045-005_02_MOL,1,LED1,
J13_3,CONN_SD-43045-005_02_MOL,1,LED2,
"J13_2, J2_2",AMASS_XT30PW-F_1x02_P2.50mm_Horizontal,2,Conn_01x02_Pin,
J14_3,PinHeader_1x03_P2.54mm_Vertical,1,Leak Sensor,
"J14, J15_2, J98, J99",PinHeader_1x08_P2.54mm_Vertical,4,Conn_01x08,
J15,CONN_SD-43045-005_04_MOL,1,Extra I2C #3,
J16_2,CONN_SD-43045-005_04_MOL,1,Extra I2C #6,
"J16, J21, J22_2",AMASS_XT60PW-F_1x02_P7.20mm_Horizontal,3,Conn_01x02_Pin,
J17,CONN_SD-43045-005_04_MOL,1,Extra I2C #5,
J18_2,CONN_SD-43045-005_04_MOL,1,Extra I2C #4,
J18,"PhoenixContact_MCV_1,5_4-G-3.81_1x04_P3.81mm_Vertical",1,Conn_01x04_Socket,
J19,PinHeader_1x10_P2.54mm_Vertical,1,GND Line,
J2,SULLINS_SBH11-PBPC-D05-ST-BK,1,Interconnect,
J20,PinHeader_1x10_P2.54mm_Vertical,1,3.3V Line,
J21_2,PinHeader_1x10_P2.54mm_Vertical,1,5V Line,
J22,CONN_SD-43045-005_06_MOL,1,Extra SPI #1,
J23,CONN_SD-43045-005_06_MOL,1,Extra SPI #2,
J24,CONN_SD-43045-005_06_MOL,1,Extra SPI #3,
J25,CONN_SD-43045-005_04_MOL,1,Secondary UART,
J3_2,AMASS_XT60PW-F_1x02_P7.20mm_Horizontal,1,External Battery,
J3,SULLINS_SBH11-PBPC-D05-ST-BK,1,SBH11-PBPC-D05-ST-BK,
"J4_2, J5, J6_2, J7",PHOENIX_1098169,4,1098169,
"J4, J6",PinHeader_1x24_P2.54mm_Vertical,2,Conn_01x24,
J5_2,AMASS_XT30PW-F_1x02_P2.50mm_Horizontal,1,External I2C,
J7_2,CONN_SD-43045-005_04_MOL,1,Extra I2C #1,
J8_2,Molex_Micro-Fit_3.0_43045-0212_2x01_P3.00mm_Vertical,1,0430450212,
J8,CONN_SD-43045-005_04_MOL,1,Extra I2C #2,
J9_2,CONN_SD-43045-005_02_MOL,1,Lumen PWM,
"Q7_3, Q7_2, Q7",TO-252-2_L6.5-W6.1-P4.58-LS10.0-TL,3,L78M05ABDT-TR,C58069
"R1_2, R10, R11, R2_2, R27, R3, R32, R34, R36, R4, R41, R5, R6, R7_2, R8_2",0805,15,10k,
"R1, R2, R29, R30, R37, R38, R39, R5_2, R6_2, R7, R8",0805,11,0R,
R28,0805,1,20k,
R3_2,2506_8x_Resistor_Array,1,2.2k Array,
"R31, R33, R35",0805,3,47k,
R4_2,2506_8x_Resistor_Array,1,3.3k Array,
"U1, U16, U2",MSOP-8_3x3mm_P0.65mm,3,MCP9808_MSOP,
"U15_2, U15, U3",SOT-223-3_TabPin2,3,AMS1117-3.3,
U17,"Allegro_MicroSystems,_LLC-CB-5-PFF-0-0-MFG",1,ACS758LCB-100U-PFF-T,
U18,TO-263-2,1,SRT60L100DC-R,
U4,Bosch_LGA-8_2.5x2.5mm_P0.65mm_ClockwisePinNumbering,1,BME280,
U6,Teensy41,1,Teensy4.1,

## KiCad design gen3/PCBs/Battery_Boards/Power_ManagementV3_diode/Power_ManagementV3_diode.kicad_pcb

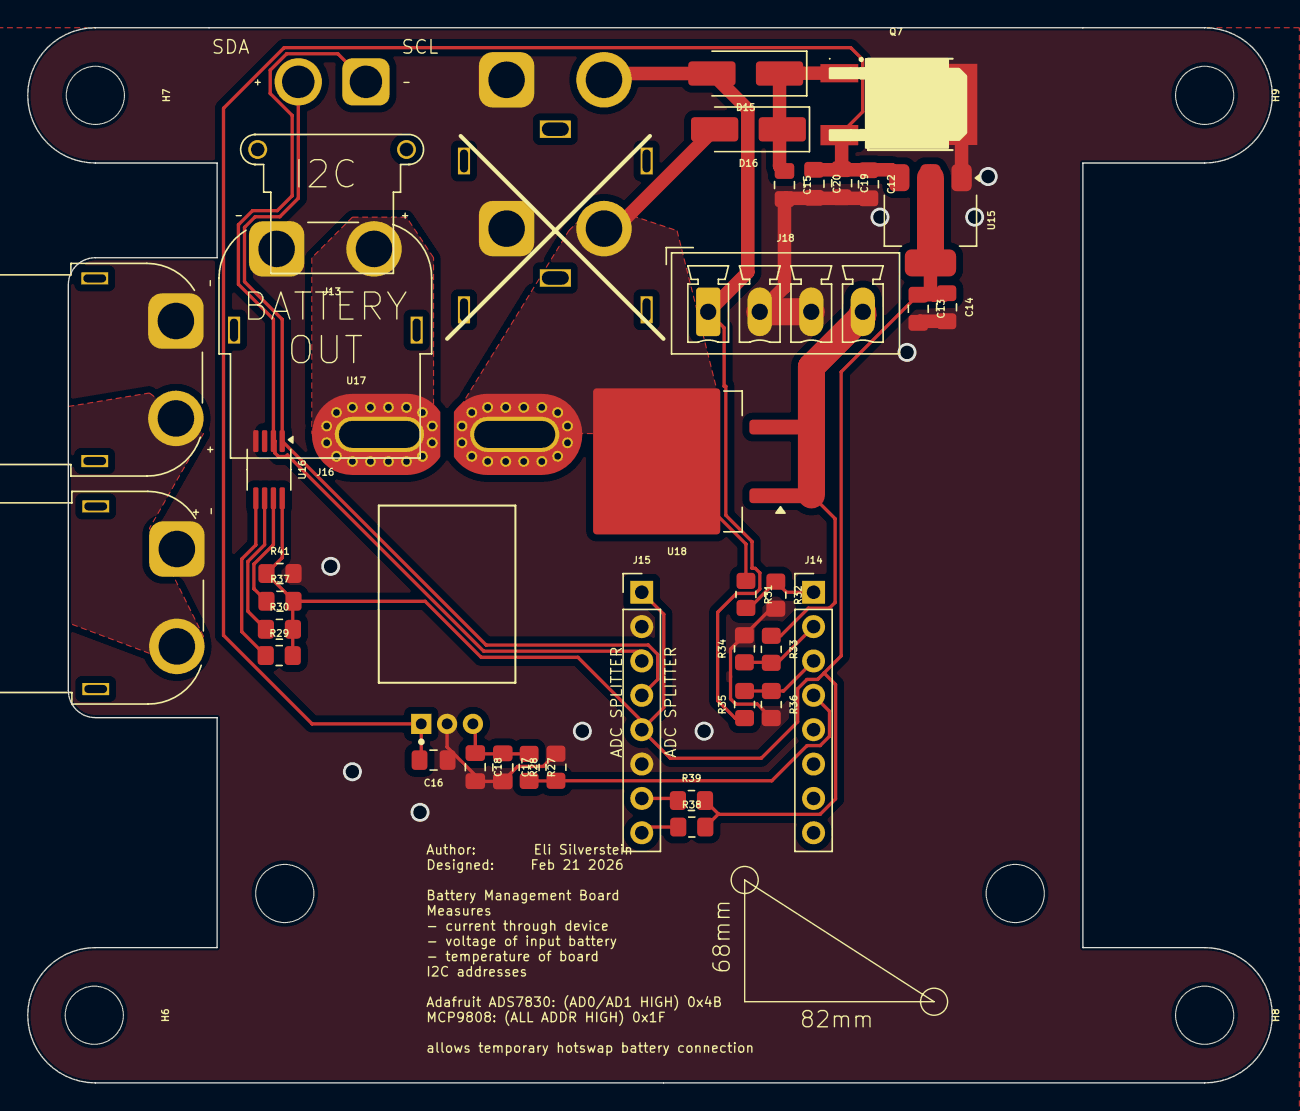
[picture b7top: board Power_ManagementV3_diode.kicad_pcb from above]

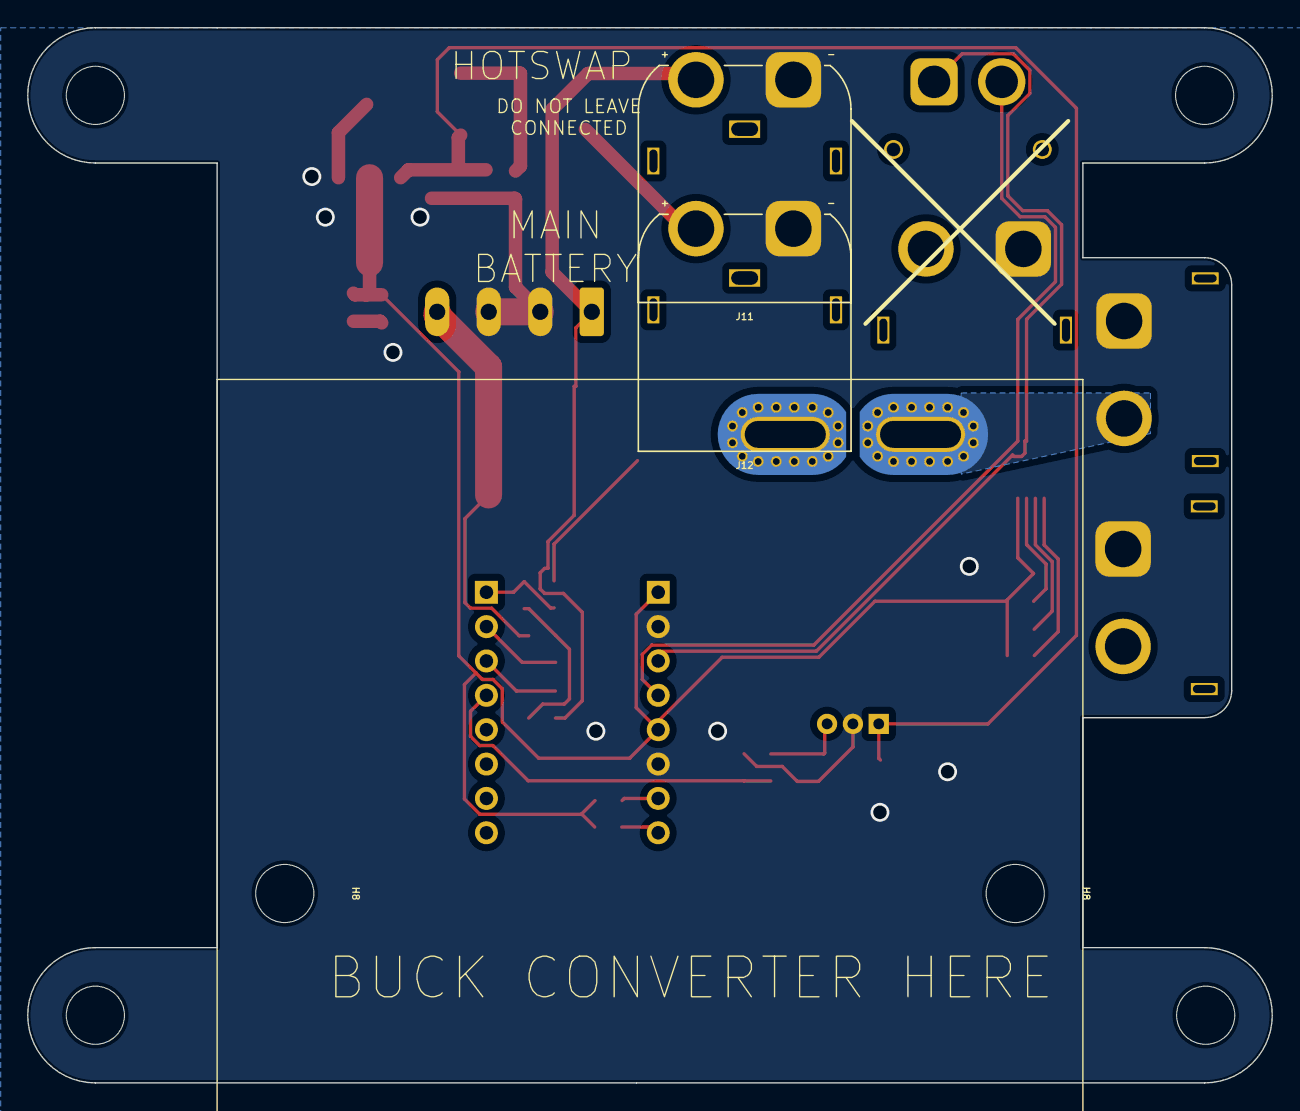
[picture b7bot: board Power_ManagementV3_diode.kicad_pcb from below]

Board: 2 copper layers, 92.0 x 78.0 mm, 45 parts (4 on the bottom side), 20 nets.

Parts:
C12, C13, C15, C19: 10uF; C_0805_2012Metric_Pad1.18x1.45mm_HandSolder
C14, C20: 1uF; C_0805_2012Metric_Pad1.18x1.45mm_HandSolder
C16: 0.1uF; C_0805_2012Metric_Pad1.18x1.45mm_HandSolder
C17: 100nF; C_0805_2012Metric_Pad1.18x1.45mm_HandSolder
C18: 1µF; C_0805_2012Metric_Pad1.18x1.45mm_HandSolder
D15, D16: SS54; D_SMA_Handsoldering
H6, H7, H8, H8#2, H8#3, H9: MountingHole; MountingHole_4.3mm_M4
J11, J12: Conn_01x02_Pin; AMASS_XT60IPW-M_1x03_P7.20mm_Horizontal
J13: Conn_01x02_Pin; AMASS_XT30PW-F_1x02_P2.50mm_Horizontal
J14, J15: Conn_01x08; PinHeader_1x08_P2.54mm_Vertical
J16, J21, J22: Conn_01x02_Pin; AMASS_XT60PW-F_1x02_P7.20mm_Horizontal
J18: Conn_01x04_Socket; PhoenixContact_MCV_1,5_4-G-3.81_1x04_P3.81mm_Vertical
Q7: L78M05ABDT-TR; TO-252-2_L6.5-W6.1-P4.58-LS10.0-TL
R27, R32, R34, R36, R41: 10k; R_0805_2012Metric_Pad1.20x1.40mm_HandSolder
R28: 20k; R_0805_2012Metric_Pad1.20x1.40mm_HandSolder
R29, R30, R37, R38, R39: 0R; R_0805_2012Metric_Pad1.20x1.40mm_HandSolder
R31, R33, R35: 47k; R_0805_2012Metric_Pad1.20x1.40mm_HandSolder
U15: AMS1117-3.3; SOT-223-3_TabPin2
U16: MCP9808_MSOP; MSOP-8_3x3mm_P0.65mm
U17: ACS758LCB-100U-PFF-T; Allegro_MicroSystems,_LLC-CB-5-PFF-0-0-MFG
U18: SRT60L100DC-R; TO-263-2

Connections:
+3.3V_: C13.1, C14.1, J15.1, J15.5, R29.2, R30.2, R37.2, R38.2, R39.2, R41.1, U15.2 (VO), U16.8 (V_{DD})
+5V_: C12.1, C16.2, C19.1, C20.1, Q7.3 (OUT), U15.3 (VI), U17.1 (VCC)
+BATT: D16.2 (A), J12.2, R31.1, U17.4 (IP+), U18.2 (Output)
+BATT_out: J16.2, J21.2, J22.2, U17.5 (IP-)
+EXT_LV_SUPPLY: J18.4, R33.1, U18.1 (Input), U18.3 (Input)
+TEMP_BATT: D15.2 (A), J11.2, J18.1, R35.1
/SCL: J13.1, J15.3, U16.2 (SCL)
/SDA: J13.2, J15.4, U16.1 (SDA)
GND_bak: C12.2, C13.2, C14.2, C15.2, C16.1, C17.2, C18.2, C19.2, C20.2, J11.1, J12.1, J15.2, J15.6, J16.1, J18.2, J18.3, J21.1, J22.1, Q7.4 (GND), R28.2, R32.2, R34.2, R36.2, R41.2, U15.1 (GND), U16.4 (GND), U17.2 (GND)
unnamed: C15.1, D15.1 (K), D16.1 (K), Q7.1 (IN)
unnamed: J14.1, R31.2, R32.1
unnamed: J14.2, R33.2, R34.1
unnamed: J14.3, R35.2, R36.1
unnamed: J15.7, R39.1
unnamed: J15.8, R38.1
unnamed: R37.1, U16.7 (A0)
unnamed: R30.1, U16.6 (A1)
unnamed: R29.1, U16.5 (A2)
current_sensor_3v3: J14.4, R27.2, R28.1
current_sensor_5v: C17.1, C18.1, R27.1, U17.3 (VIOUT)

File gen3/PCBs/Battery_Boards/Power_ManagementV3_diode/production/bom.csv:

Designator,Footprint,Quantity,Value,LCSC Part #
"C12, C13, C15, C19",0805,4,10uF,
"C14, C20",0805,2,1uF,
C16,0805,1,0.1uF,
C17,0805,1,100nF,
C18,0805,1,1µF,
"D15, D16",D_SMA_Handsoldering,2,SS54,
"H6, H7, H8_3, H8_2, H8, H9",MountingHole_4.3mm_M4,6,MountingHole,
"J11, J12",AMASS_XT60IPW-M_1x03_P7.20mm_Horizontal,2,Conn_01x02_Pin,
J13,AMASS_XT30PW-F_1x02_P2.50mm_Horizontal,1,Conn_01x02_Pin,
"J14, J15",PinHeader_1x08_P2.54mm_Vertical,2,Conn_01x08,
"J16, J21, J22",AMASS_XT60PW-F_1x02_P7.20mm_Horizontal,3,Conn_01x02_Pin,
J18,"PhoenixContact_MCV_1,5_4-G-3.81_1x04_P3.81mm_Vertical",1,Conn_01x04_Socket,
Q7,TO-252-2_L6.5-W6.1-P4.58-LS10.0-TL,1,L78M05ABDT-TR,C58069
"R27, R32, R34, R36, R41",0805,5,10k,
R28,0805,1,20k,
"R29, R30, R37, R38, R39",0805,5,0R,
"R31, R33, R35",0805,3,47k,
U15,SOT-223-3_TabPin2,1,AMS1117-3.3,
U16,MSOP-8_3x3mm_P0.65mm,1,MCP9808_MSOP,
U17,"Allegro_MicroSystems,_LLC-CB-5-PFF-0-0-MFG",1,ACS758LCB-100U-PFF-T,
U18,TO-263-2,1,SRT60L100DC-R,

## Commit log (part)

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2025-11-12 added internal temperature to STABLE
2026-02-21 refractored code
2026-02-21 test file
2026-02-21 added gen3 board
2026-02-21 test message
2026-02-21 reformated and refactored micro pcb board
2026-02-21 adding Battery_Boards directory
2026-02-21 Add shared robosub KiCad libraries, importorted 5v regulator, made some changes to battery management board
2026-02-21 power dist fixes 1
2026-02-21 power distttt
2026-02-21 initial designs
2026-02-22 schematics of microboard done
2026-02-22 fixed up the battery board. should be good to order soon
2026-02-22 added caps to micro breakout
2026-02-22 added back 5V regulator footprints
2026-02-22 microcontroller breakout board completed!!
2026-02-22 power dist board
2026-02-22 bms board finished
2026-02-25 power dist final?
2026-02-25 added to_order
2026-02-25 fixed pinout for ribbon
2026-02-25 fixed GND plane
2026-02-27 to_order has the 3 main pcbs consolidated. pcbs have been put into production
2026-04-08 connected missing SDA SCL connection on gen 3 micro board
2026-04-15 added all custom in robosub_3d_models
2026-04-15 no errors for updating symbol
2026-04-15 works
2026-04-15 jlc_to_robosub working, and all parts are updated.
2026-04-15 updated parts to include jlcpcb as library path
2026-04-15 deleted and renamed unnecessary step and footprints
2026-04-15 fixed
2026-04-15 jlc_to_robosub is completely working
2026-04-15 edited spreadsheet
2026-04-15 Updated the whole schematic to now include 3d model
2026-04-21 wired correctly gen3 sub
2026-04-21 editted
2026-04-22 some notes to self in new board
2026-04-29 fixed cap on microbreakout
2026-05-20 power distribution board updates
